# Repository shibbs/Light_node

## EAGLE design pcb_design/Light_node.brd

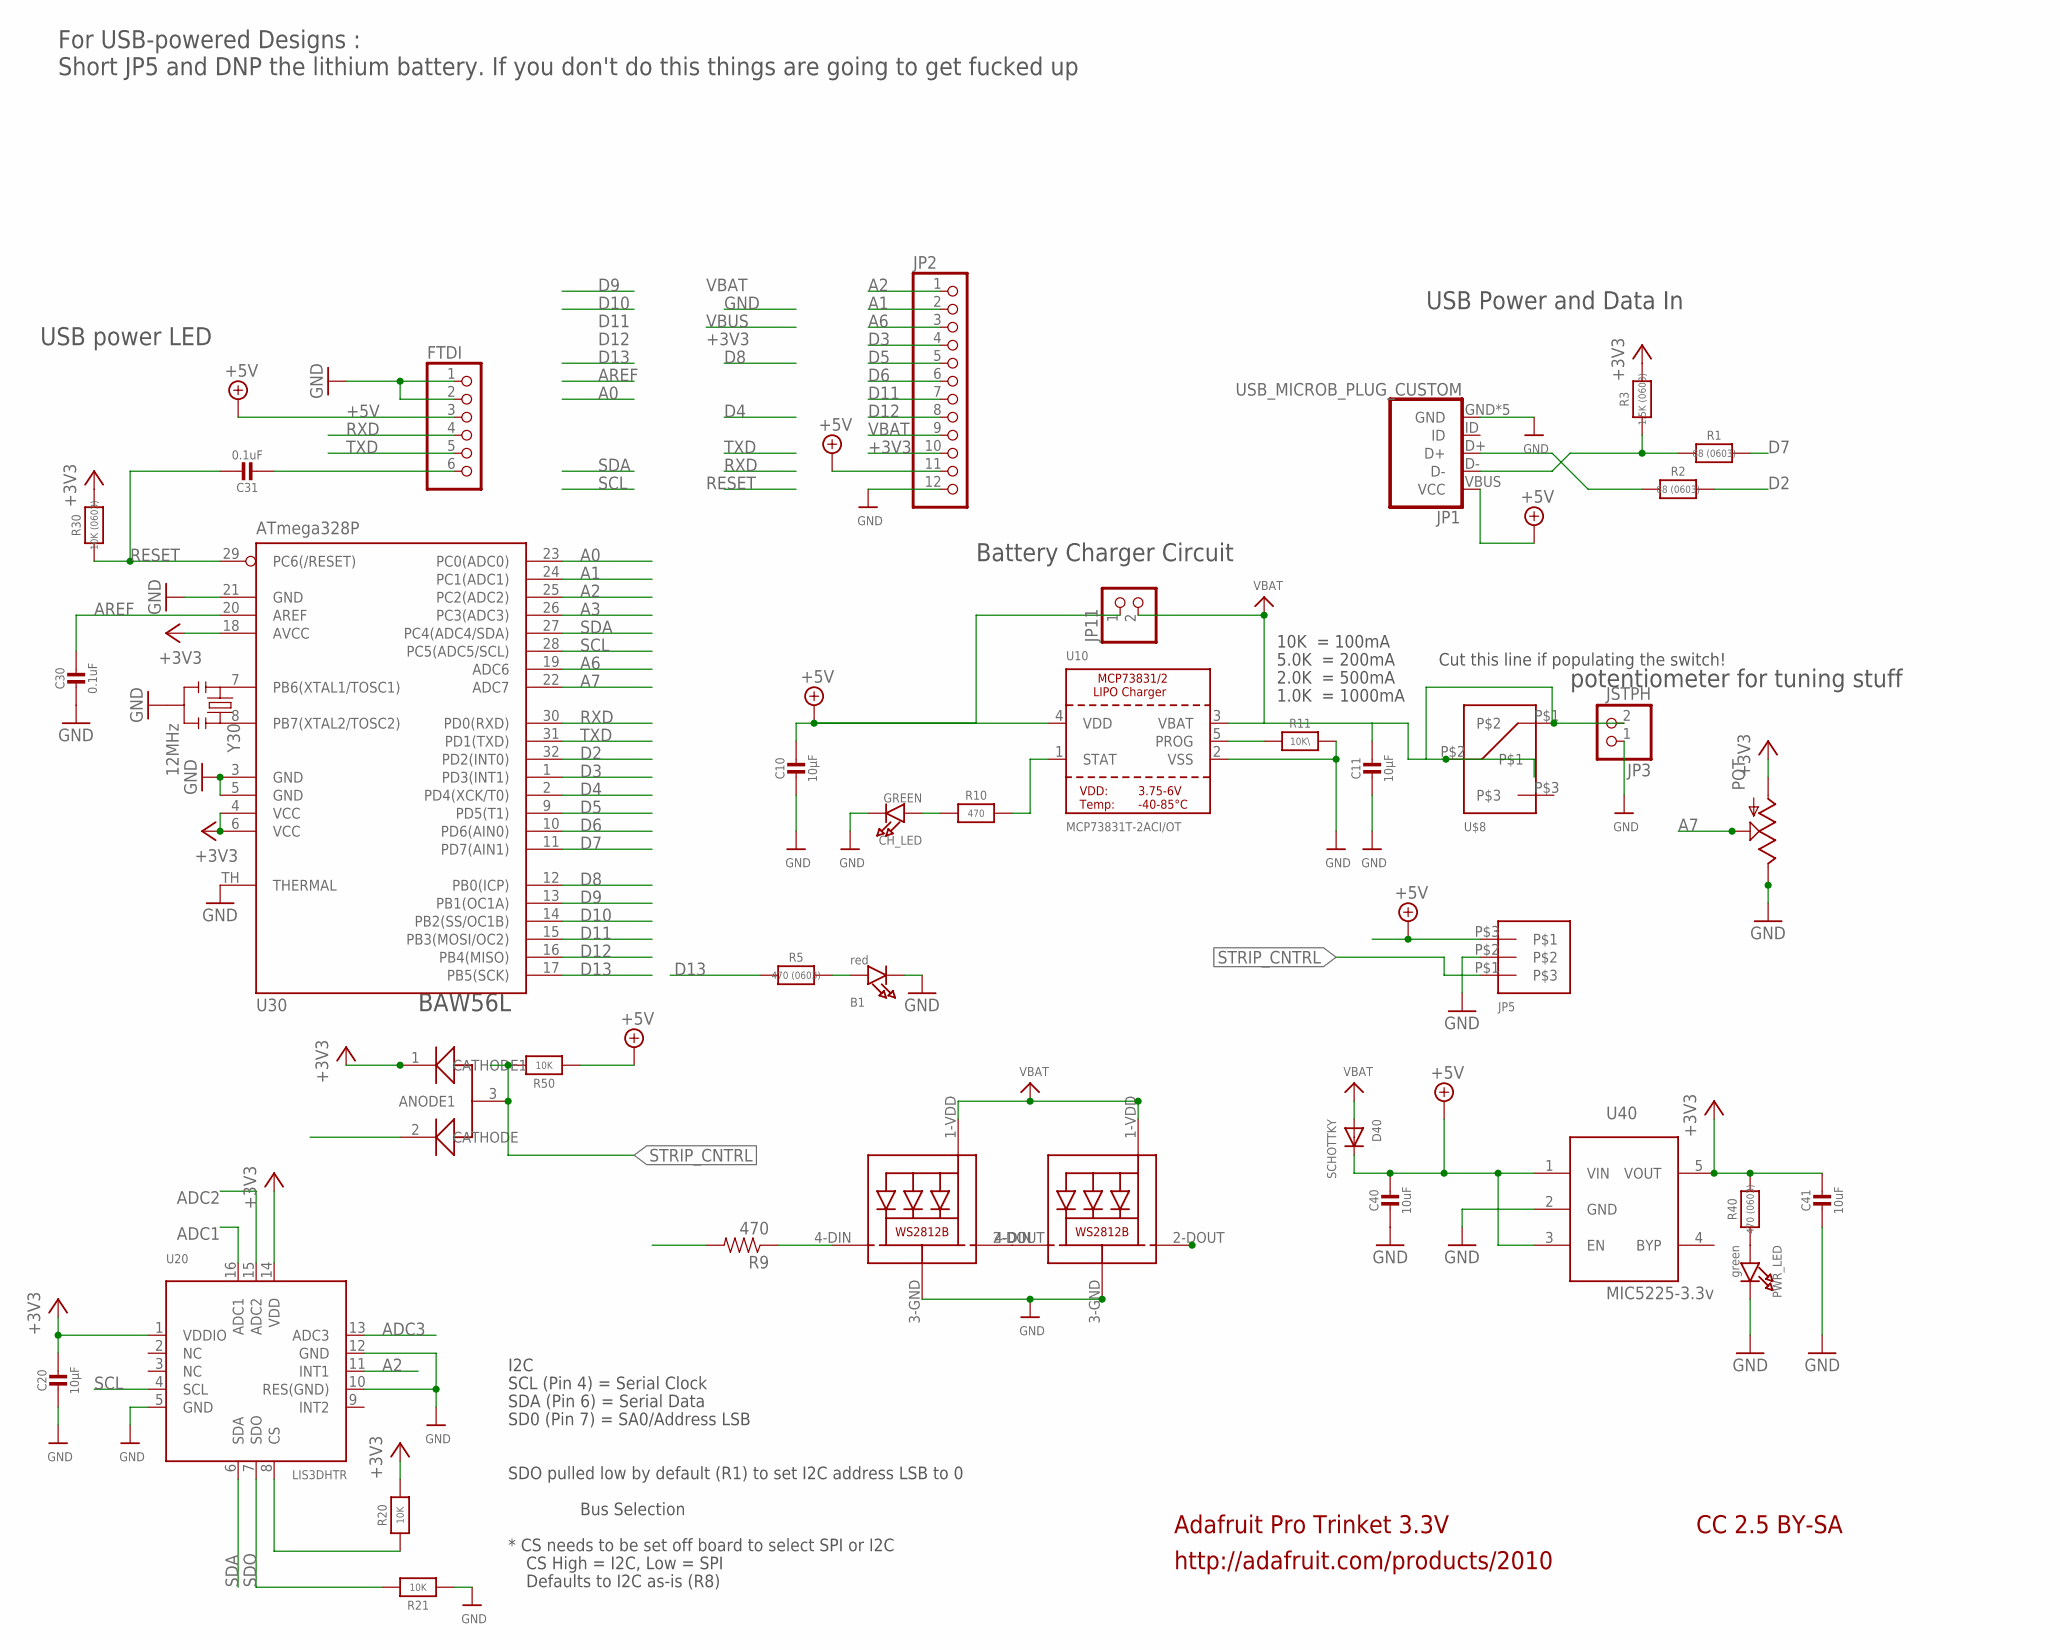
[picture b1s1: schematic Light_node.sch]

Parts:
B1: red; CHIPLED_0805_NOOUTLINE
C10, C11, C20: 10µF; 0805-NO
C30: 0.1uF; _0805MP
C31: 0.1uF; 0805-NO
C40, C41: 10uF; 0805-NO
CH_LED: GREEN; CHIPLED_0805_NOOUTLINE
D40: SCHOTTKY; SOD-123FL
FTDI: PINHD-1X6CB; 1X06-CLEANBIG
JP1: USB_MICROB_PLUG_CUSTOM; USB-MICROB
JP2: PINHD-1X12-CB; 1X12-CB
JP3: JSTPH; JSTPH2
JP5: M03; M03_25MM
JP11: HEADER-1X2ROUND; 1X02_ROUND
POT: POT; 3306P_POT
PWR_LED: green; CHIPLED_0805_NOOUTLINE
R1, R2: 68 (0603); 0603-NO
R3: 1.5K (0603); 0603-NO
R5, R40: 470 (0603); 0603-NO
R9: 470; 0603-RES
R10: 470; 0805-NO
R11: 10K\; 0805-NO
R20, R21: 10K; 0805-NO
R30: 10K (0603); 0805-NO
R50: 10K; 0603-NO
RGB1, RGB2: WS2812B5050; WS2812B
U10: MCP73831T-2ACI/OT; SOT23-5
U20: LIS3DHTR; LGA16_3X3MM
U30: ATmega328P; MLF32-TH
U40: MIC5225-3.3v; SOT23-5L
U50: COMMON_ANODE_DIODE; SOT23
U$8: SPDT_NO_GNDSMT; JS102011SAQN
Y30: 12MHz; RESONATOR-SMD

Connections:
+3V3: C20.1, C41.1, JP2.10, POT.P$1 (A), R3.2, R20.2, R30.2, R40.2, U20.1 (VDDIO), U20.14 (VDD), U30.4 (VCC), U30.6 (VCC), U30.18 (AVCC), U40.5 (VOUT), U50.1 (CATHODE1)
+5V: C10.1, C40.1, D40.C, FTDI.3, JP1.VBUS (VCC), JP2.11, JP5.P$3, JP11.1, R50.1, U10.4 (VDD), U40.1 (VIN), U40.3 (EN)
A0: U30.23 (PC0(ADC0))
A1: JP2.2, U30.24 (PC1(ADC1))
A2: JP2.1, U20.11 (INT1), U30.25 (PC2(ADC2))
A3: U30.26 (PC3(ADC3))
A6: JP2.3, U30.19 (ADC6)
A7: POT.P$3 (S), U30.22 (ADC7)
ADC1: U20.16 (ADC1)
ADC2: U20.15 (ADC2)
ADC3: U20.13 (ADC3)
AREF: C30.1, U30.20 (AREF)
CS: R20.1, U20.8 (CS)
D2: R2.2, U30.32 (PD2(INT0))
D3: JP2.4, U30.1 (PD3(INT1))
D4: U30.2 (PD4(XCK/T0)), U50.2 (CATHODE)
D5: JP2.5, U30.9 (PD5(T1))
D6: JP2.6, U30.10 (PD6(AIN0))
D7: R1.2, U30.11 (PD7(AIN1))
D8: U30.12 (PB0(ICP))
D9: U30.13 (PB1(OC1A))
D10: R9.2, U30.14 (PB2(SS/OC1B))
D11: JP2.7, U30.15 (PB3(MOSI/OC2))
D12: JP2.8, U30.16 (PB4(MISO))
D13: R5.2, U30.17 (PB5(SCK))
D+: JP1.D+, R2.1
D-: JP1.D-, R1.1, R3.1
DTR/RTS: C31.2, FTDI.6
GND: B1.C, C10.2, C11.2, C20.2, C30.2, C40.2, C41.2, CH_LED.C, FTDI.1, FTDI.2, JP1.GND, JP1.P$1 (GND), JP1.P$2 (GND), JP1.P$3 (GND), JP1.P$4 (GND), JP2.12, JP3.1, JP5.P$2, POT.P$2 (E), PWR_LED.C, R11.2, R21.1, RGB1.3-GND (GND), RGB2.3-GND (GND), U10.2 (VSS), U20.5 (GND), U20.10 (RES(GND)), U20.12 (GND), U30.3 (GND), U30.5 (GND), U30.21 (GND), U30.TH (THERMAL), U40.2 (GND), Y30.2
LED_CNTRL: R9.1, RGB1.4-DIN (DI)
unnamed: B1.A, R5.1
unnamed: U30.8 (PB7(XTAL2/TOSC2)), Y30.3
unnamed: U30.7 (PB6(XTAL1/TOSC1)), Y30.1
unnamed: RGB1.2-DOUT (DO), RGB2.4-DIN (DI)
unnamed: R10.2, U10.1 (STAT)
unnamed: PWR_LED.A, R40.1
unnamed: R11.1, U10.5 (PROG)
unnamed: CH_LED.A, R10.1
RESET: C31.1, R30.1, U30.29 (PC6(/RESET))
RXD: FTDI.4, U30.30 (PD0(RXD))
SCL: U20.4 (SCL), U30.28 (PC5(ADC5/SCL))
SDA: U20.6 (SDA), U30.27 (PC4(ADC4/SDA))
SDO: R21.2, U20.7 (SDO)
STRIP_CNTRL: JP5.P$1, R50.2, U50.3 (ANODE1)
TXD: FTDI.5, U30.31 (PD1(TXD))
VBAT: C11.1, D40.A, JP2.9, JP3.2, JP11.2, RGB1.1-VDD (VDD), RGB2.1-VDD (VDD), U10.3 (VBAT), U$8.P$1, U$8.P$2

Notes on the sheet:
Adafruit Pro Trinket 3.3V
http://adafruit.com/products/2010
CC 2.5 BY-SA
10K = 100mA
5.0K = 200mA
2.0K = 500mA
1.0K = 1000mA
Battery Charger Circuit
USB power LED
USB Power and Data In
potentiometer for tuning stuff
I2C
SCL (Pin 4) = Serial Clock
SDA (Pin 6) = Serial Data
SD0 (Pin 7) = SA0/Address LSB
* CS needs to be set off board to select SPI or I2C
CS High = I2C, Low = SPI
Defaults to I2C as-is (R8)
SDO pulled low by default (R1) to set I2C address LSB to 0
Bus Selection
For USB-powered Designs : Short JP5 and DNP the lithium battery. If you don't do this things are going to get fucked up
BAW56L
Cut this line if populating the switch!

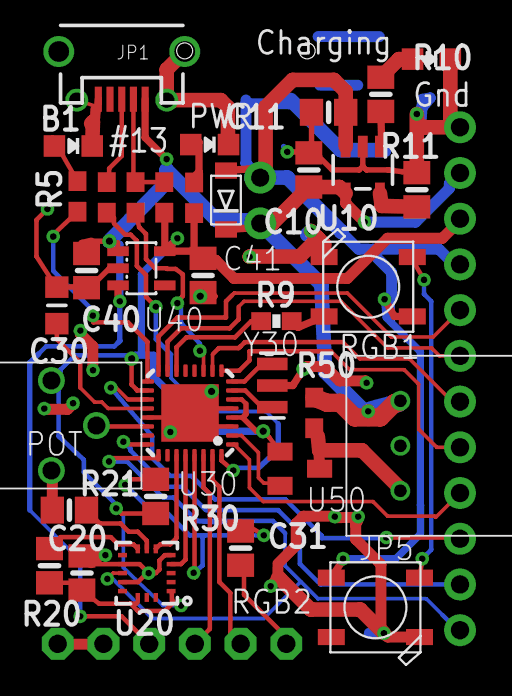
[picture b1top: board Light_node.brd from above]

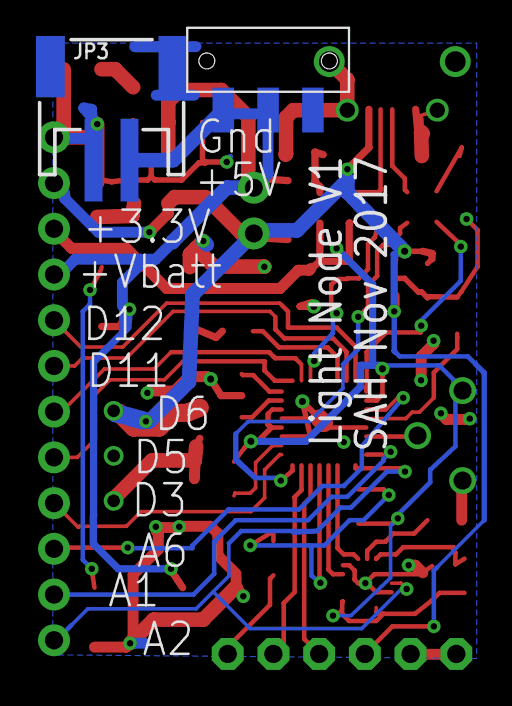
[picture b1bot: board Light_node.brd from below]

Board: 2 copper layers, 39 parts (2 on the bottom side), 39 nets.

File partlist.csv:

Partlist

Exported from Light_node.sch at 11/29/17 4:14 PM

EAGLE Version 7.5.0 Copyright (c) 1988-2015 CadSoft

Assembly variant: 

Part     Value                  Device                    Package                Library      Sheet

B1       red                    LED0805_NOOUTLINE         CHIPLED_0805_NOOUTLINE microbuilder 1
C10      10µF                   CAP_CERAMIC0805-NOOUTLINE 0805-NO                microbuilder 1
C11      10µF                   CAP_CERAMIC0805-NOOUTLINE 0805-NO                microbuilder 1
C20      10µF                   CAP_CERAMIC0805-NOOUTLINE 0805-NO                microbuilder 1
C30      0.1uF                  CAP_CERAMIC_0805MP        _0805MP                microbuilder 1
C31      0.1uF                  CAP_CERAMIC0805-NOOUTLINE 0805-NO                microbuilder 1
C40      10uF                   CAP_CERAMIC0805-NOOUTLINE 0805-NO                microbuilder 1
C41      10uF                   CAP_CERAMIC0805-NOOUTLINE 0805-NO                microbuilder 1
CH_LED   GREEN                  LED0805_NOOUTLINE         CHIPLED_0805_NOOUTLINE microbuilder 1
D40      SCHOTTKY               DIODE_SOD-123FL           SOD-123FL              adafruit     1
FTDI                            PINHD-1X6CB               1X06-CLEANBIG          adafruit     1
JP1      USB_MICROB_PLUG_CUSTOM USB_MICROB_PLUG_CUSTOM    USB-MICROB             0_AlpineLabs 1
JP2                             PINHD-1X12-CB             1X12-CB                adafruit     1
JP3      JSTPH                  JST_2PIN                  JSTPH2                 microbuilder 1
JP5      M03                    M03                       M03_25MM               0_Shibbs1    1
JP11                            HEADER-1X2ROUND           1X02_ROUND             microbuilder 1
POT                             POT                       3306P_POT              0_Shibbs1    1
PWR_LED  green                  LED0805_NOOUTLINE         CHIPLED_0805_NOOUTLINE microbuilder 1
R1       68 (0603)              RESISTOR_0603_NOOUT       0603-NO                microbuilder 1
R2       68 (0603)              RESISTOR_0603_NOOUT       0603-NO                microbuilder 1
R3       1.5K (0603)            RESISTOR_0603_NOOUT       0603-NO                microbuilder 1
R5       470 (0603)             RESISTOR_0603_NOOUT       0603-NO                microbuilder 1
R9       100                    RESISTOR_0603_NOOUT       0603-NO                microbuilder 1
R10      470                    RESISTOR0805_NOOUTLINE    0805-NO                microbuilder 1
R11      10K\                   RESISTOR0805_NOOUTLINE    0805-NO                microbuilder 1
R20      10K                    RESISTOR0805_NOOUTLINE    0805-NO                microbuilder 1
R21      10K                    RESISTOR0805_NOOUTLINE    0805-NO                microbuilder 1
R30      10K (0603)             RESISTOR0805_NOOUTLINE    0805-NO                microbuilder 1
R40      470 (0603)             RESISTOR_0603_NOOUT       0603-NO                microbuilder 1
R50      10K                    RESISTOR_0603_NOOUT       0603-NO                microbuilder 1
RGB1     WS2812B5050            WS2812B5050               WS2812B                microbuilder 1
RGB2     WS2812B5050            WS2812B5050               WS2812B                microbuilder 1
U$8      SPDT_NO_GNDSMT         SPDT_NO_GNDSMT            JS102011SAQN           0_Shibbs1    1
U10      MCP73831T-2ACI/OT      MCP73831/2                SOT23-5                microbuilder 1
U20      LIS3DHTR               ACCEL_LIS3DHTR            LGA16_3X3MM            microbuilder 1
U30      ATmega328P             MEGA8-MI                  MLF32-TH               microbuilder 1
U40      MIC5225-3.3v           LP298XS                   SOT23-5L               adafruit     1
U50      COMMON_ANODE_DIODE     COMMON_ANODE_DIODE        SOT23                  0_AlpineLabs 1
Y30      12MHz                  RESONATORSMD              RESONATOR-SMD          SparkFun     1

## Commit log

2017-11-07 Initial commit!
2017-11-07 Pulled the regulator components
2017-11-10 added a bunch of new stuff in
2017-11-10 jumpe us over to using the 3.3V version of the promicro
2017-11-10 added in the accelerometer and removed the Reset pin
2017-11-10 committed adafruit readme
2017-11-10 updated gitignore but doesn't seem to work well
2017-11-10 most of the layour is completed using standard LEDs, but we should move to neopixels on board
2017-11-10 moved us to neopixels, added breakout headers, almost done
2017-11-10 stopped trackikng the autosave files
2017-11-13 moced some parts around
2017-11-14 Things are pretty close to complete
2017-11-14 added the switch to the bottom
2017-11-21 V1 Release!!
2017-12-17 got the boards running and initial code is working well!!!
2017-12-17 Updated the code a bit to handle Z a bit better
2017-12-18 some code, some documentation
2017-12-18 Added README to get people started.
2017-12-19 Updated a lot of code. Got things working pretty well, but this actually relies on a library that sits in the arduino library folder
2018-02-01 updated some documentation and did some testing
2018-02-02 updating things to Steve_stripper is running with my spirit hood well using motion to trigger pulses
2018-02-03 Moved the Library folder and files into this level of the repo and then symlinked from the Arduino Libraries folder to make sure everyhing syncs and tracks better Updated the documentation accordingl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
2018-02-03 Cleaned up the power save function and may have fixed it. Cleaned up soem general code stuff as well, added masks instead of magic numbers for masking operations

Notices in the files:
parts and their libraries:
microbuilder: This work is placed in the public domain, and may be freely used for commercial and non-commercial work with the following conditions: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
SparkFun: Licensing: CC v3.0 Share-Alike You are welcome to use this library for commercial purposes.
